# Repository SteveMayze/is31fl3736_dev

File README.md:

# IS31FL3736 Development Board

This project is to develop a prototype for reviewing the IS31FL3736 12×8 DOTS MATRIX LED DRIVER WITH INDIVIDUAL AUTO BREATH FUNCTION from [Integrated Silicon Solution, Inc](www.issi.com)
 The basic goals of this project is to create a simple board with an array of RGB leds to see what is involved to control the LEDs as per the writeup in the datasheet. Things of interest will be
 
 1. Simplicity of use (firmware)
 1. Simplicity of the layout
 1. The effective power consumption
 1. The footprint size.

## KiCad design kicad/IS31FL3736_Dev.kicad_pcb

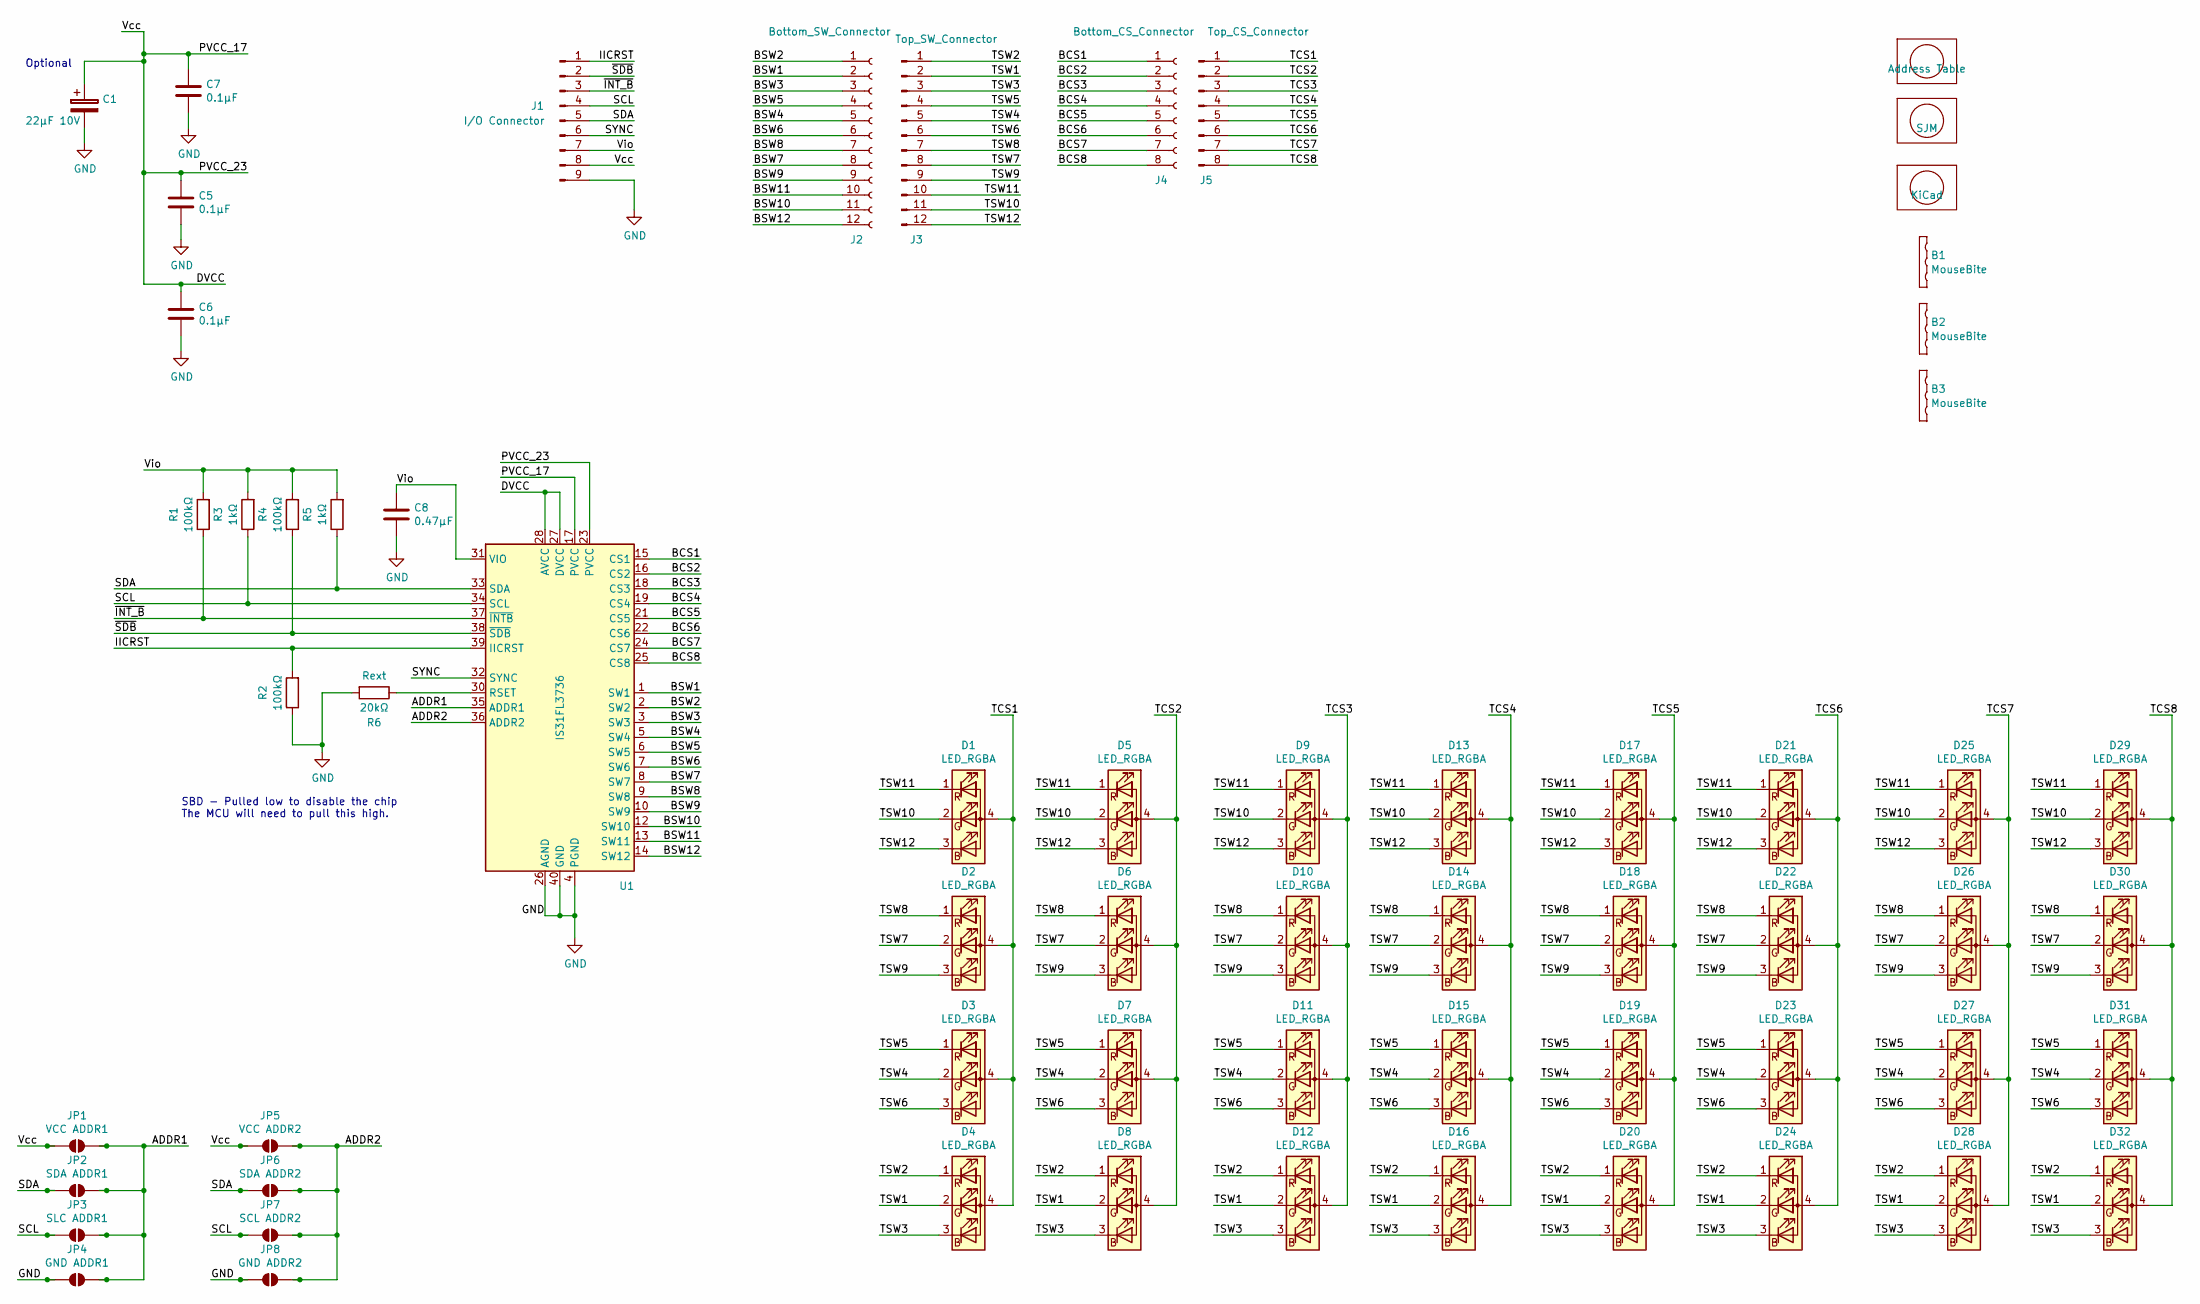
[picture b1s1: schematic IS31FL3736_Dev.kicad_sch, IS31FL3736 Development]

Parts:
B1, B2, B3: MouseBite; MouseBites
C1: 22μF 10V; CP_EIA-2012-15_AVX-P
C5, C6, C7: 0.1μF; C_0805_2012Metric
C8: 0.47μF; C_0805_2012Metric
D1, D2, D3, D4, D5, D6, D7, D8, D9, D10, D11, D12, D13, D14, D15, D16, D17, D18, D19, D20, D21, D22, D23, D24, D25, D26, D27, D28, D29, D30, D31, D32: LED_RGBA; LED_RGB_4-PLCC; MPN AAA3528LSEEZGKQBKS
J1: I/O Connector; PinHeader_1x09_P2.54mm_Horizontal
J2: Bottom_SW_Connector; PinSocket_1x12_P2.54mm_Vertical
J3: Top_SW_Connector; PinHeader_1x12_P2.54mm_Vertical
J4: Bottom_CS_Connector; PinSocket_1x08_P2.54mm_Vertical
J5: Top_CS_Connector; PinHeader_1x08_P2.54mm_Vertical
JP1: VCC ADDR1; SolderJumper-2_P1.3mm_Open_RoundedPad1.0x1.5mm
JP2: SDA ADDR1; SolderJumper-2_P1.3mm_Open_RoundedPad1.0x1.5mm
JP3: SLC ADDR1; SolderJumper-2_P1.3mm_Open_RoundedPad1.0x1.5mm
JP4: GND ADDR1; SolderJumper-2_P1.3mm_Open_RoundedPad1.0x1.5mm
JP5: VCC ADDR2; SolderJumper-2_P1.3mm_Open_RoundedPad1.0x1.5mm
JP6: SDA ADDR2; SolderJumper-2_P1.3mm_Open_RoundedPad1.0x1.5mm
JP7: SCL ADDR2; SolderJumper-2_P1.3mm_Open_RoundedPad1.0x1.5mm
JP8: GND ADDR2; SolderJumper-2_P1.3mm_Open_RoundedPad1.0x1.5mm
Lg1: SJM; MyBasic_rounded_50_1
Lg2: KiCad; KiCad-Logo2_5mm_SilkScreen
Lg3: Address Table; Address_Table
R1, R2, R4: 100kΩ; R_0805_2012Metric
R3, R5: 1kΩ; R_0805_2012Metric
R6: 20kΩ; R_0805_2012Metric
U1: IS31FL3736; QFN-40-1EP_5x5mm_P0.4mm_EP3.6x3.6mm; MPN IS31FL3736

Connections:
/ADDR1: JP1.2 (B), JP2.2 (B), JP3.2 (B), JP4.2 (B), U1.35 (ADDR1)
/ADDR2: JP5.2 (B), JP6.2 (B), JP7.2 (B), JP8.2 (B), U1.36 (ADDR2)
/BCS1: J4.1, U1.15 (CS1)
/BCS2: J4.2, U1.16 (CS2)
/BCS3: J4.3, U1.18 (CS3)
/BCS4: J4.4, U1.19 (CS4)
/BCS5: J4.5, U1.21 (CS5)
/BCS6: J4.6, U1.22 (CS6)
/BCS7: J4.7, U1.24 (CS7)
/BCS8: J4.8, U1.25 (CS8)
/BSW1: J2.2, U1.1 (SW1)
/BSW2: J2.1, U1.2 (SW2)
/BSW3: J2.3, U1.3 (SW3)
/BSW4: J2.5, U1.5 (SW4)
/BSW5: J2.4, U1.6 (SW5)
/BSW6: J2.6, U1.7 (SW6)
/BSW7: J2.8, U1.8 (SW7)
/BSW8: J2.7, U1.9 (SW8)
/BSW9: J2.9, U1.10 (SW9)
/BSW10: J2.11, U1.12 (SW10)
/BSW11: J2.10, U1.13 (SW11)
/BSW12: J2.12, U1.14 (SW12)
/DVCC: C1.1, C5.1, C6.1, C7.1, J1.8, JP1.1 (A), JP5.1 (A), U1.17 (PVCC), U1.23 (PVCC), U1.27 (DVCC), U1.28 (AVCC)
/IICRST: J1.1, R2.2, U1.39 (IICRST)
/SCL: J1.4, JP3.1 (A), JP7.1 (A), R3.1, U1.34 (SCL)
/SDA: J1.5, JP2.1 (A), JP6.1 (A), R5.1, U1.33 (SDA)
/SYNC: J1.6, U1.32 (SYNC)
/TCS1: D1.4 (A), D2.4 (A), D3.4 (A), D4.4 (A), J5.1
/TCS2: D5.4 (A), D6.4 (A), D7.4 (A), D8.4 (A), J5.2
/TCS3: D9.4 (A), D10.4 (A), D11.4 (A), D12.4 (A), J5.3
/TCS4: D13.4 (A), D14.4 (A), D15.4 (A), D16.4 (A), J5.4
/TCS5: D17.4 (A), D18.4 (A), D19.4 (A), D20.4 (A), J5.5
/TCS6: D21.4 (A), D22.4 (A), D23.4 (A), D24.4 (A), J5.6
/TCS7: D25.4 (A), D26.4 (A), D27.4 (A), D28.4 (A), J5.7
/TCS8: D29.4 (A), D30.4 (A), D31.4 (A), D32.4 (A), J5.8
/TSW1: D4.2 (GK), D8.2 (GK), D12.2 (GK), D16.2 (GK), D20.2 (GK), D24.2 (GK), D28.2 (GK), D32.2 (GK), J3.2
/TSW2: D4.1 (RK), D8.1 (RK), D12.1 (RK), D16.1 (RK), D20.1 (RK), D24.1 (RK), D28.1 (RK), D32.1 (RK), J3.1
/TSW3: D4.3 (BK), D8.3 (BK), D12.3 (BK), D16.3 (BK), D20.3 (BK), D24.3 (BK), D28.3 (BK), D32.3 (BK), J3.3
/TSW4: D3.2 (GK), D7.2 (GK), D11.2 (GK), D15.2 (GK), D19.2 (GK), D23.2 (GK), D27.2 (GK), D31.2 (GK), J3.5
/TSW5: D3.1 (RK), D7.1 (RK), D11.1 (RK), D15.1 (RK), D19.1 (RK), D23.1 (RK), D27.1 (RK), D31.1 (RK), J3.4
/TSW6: D3.3 (BK), D7.3 (BK), D11.3 (BK), D15.3 (BK), D19.3 (BK), D23.3 (BK), D27.3 (BK), D31.3 (BK), J3.6
/TSW7: D2.2 (GK), D6.2 (GK), D10.2 (GK), D14.2 (GK), D18.2 (GK), D22.2 (GK), D26.2 (GK), D30.2 (GK), J3.8
/TSW8: D2.1 (RK), D6.1 (RK), D10.1 (RK), D14.1 (RK), D18.1 (RK), D22.1 (RK), D26.1 (RK), D30.1 (RK), J3.7
/TSW9: D2.3 (BK), D6.3 (BK), D10.3 (BK), D14.3 (BK), D18.3 (BK), D22.3 (BK), D26.3 (BK), D30.3 (BK), J3.9
/TSW10: D1.2 (GK), D5.2 (GK), D9.2 (GK), D13.2 (GK), D17.2 (GK), D21.2 (GK), D25.2 (GK), D29.2 (GK), J3.11
/TSW11: D1.1 (RK), D5.1 (RK), D9.1 (RK), D13.1 (RK), D17.1 (RK), D21.1 (RK), D25.1 (RK), D29.1 (RK), J3.10
/TSW12: D1.3 (BK), D5.3 (BK), D9.3 (BK), D13.3 (BK), D17.3 (BK), D21.3 (BK), D25.3 (BK), D29.3 (BK), J3.12
/Vio: C8.1, J1.7, R1.2, R3.2, R4.2, R5.2, U1.31 (VIO)
/~INT_B: J1.3, R1.1, U1.37 (~INTB)
/~SDB: J1.2, R4.1, U1.38 (~SDB)
GND: C1.2, C5.2, C6.2, C7.2, C8.2, J1.9, JP4.1 (A), JP8.1 (A), R2.1, R6.2, U1.4 (PGND), U1.11 (PGND), U1.26 (AGND), U1.40 (GND), U1.41 (GND)
unnamed: R6.1, U1.30 (RSET)

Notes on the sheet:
SBD - Pulled low to disable the chip The MCU will need to pull this high.
Optional

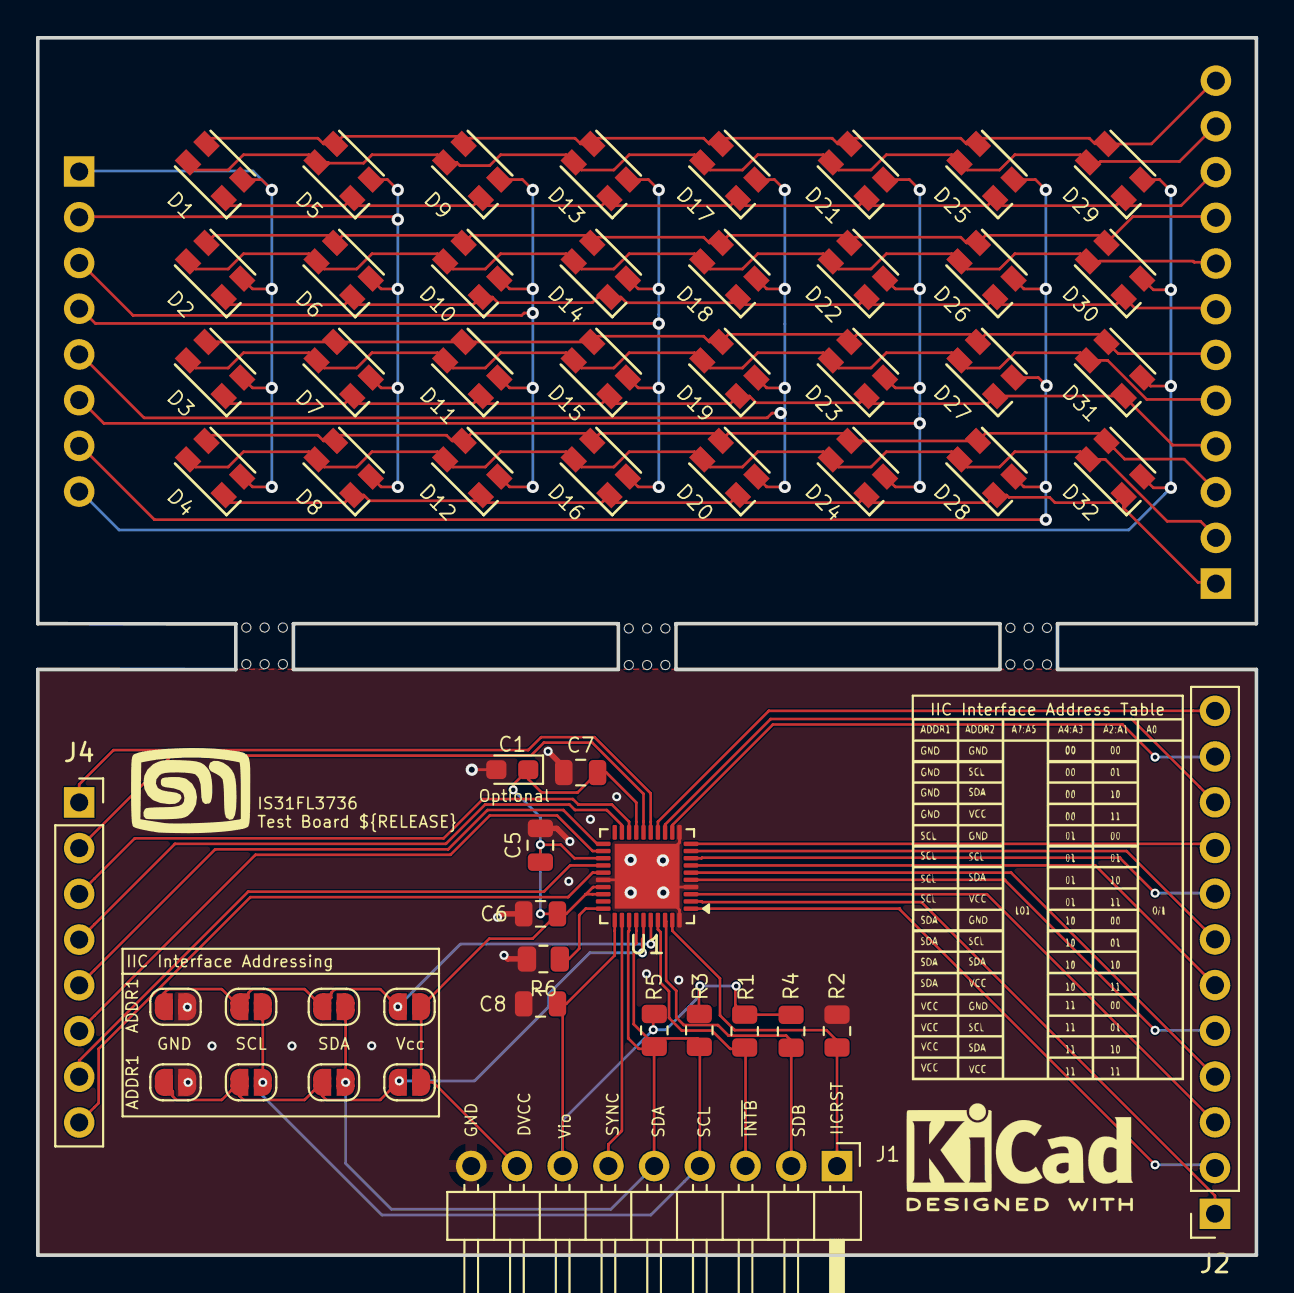
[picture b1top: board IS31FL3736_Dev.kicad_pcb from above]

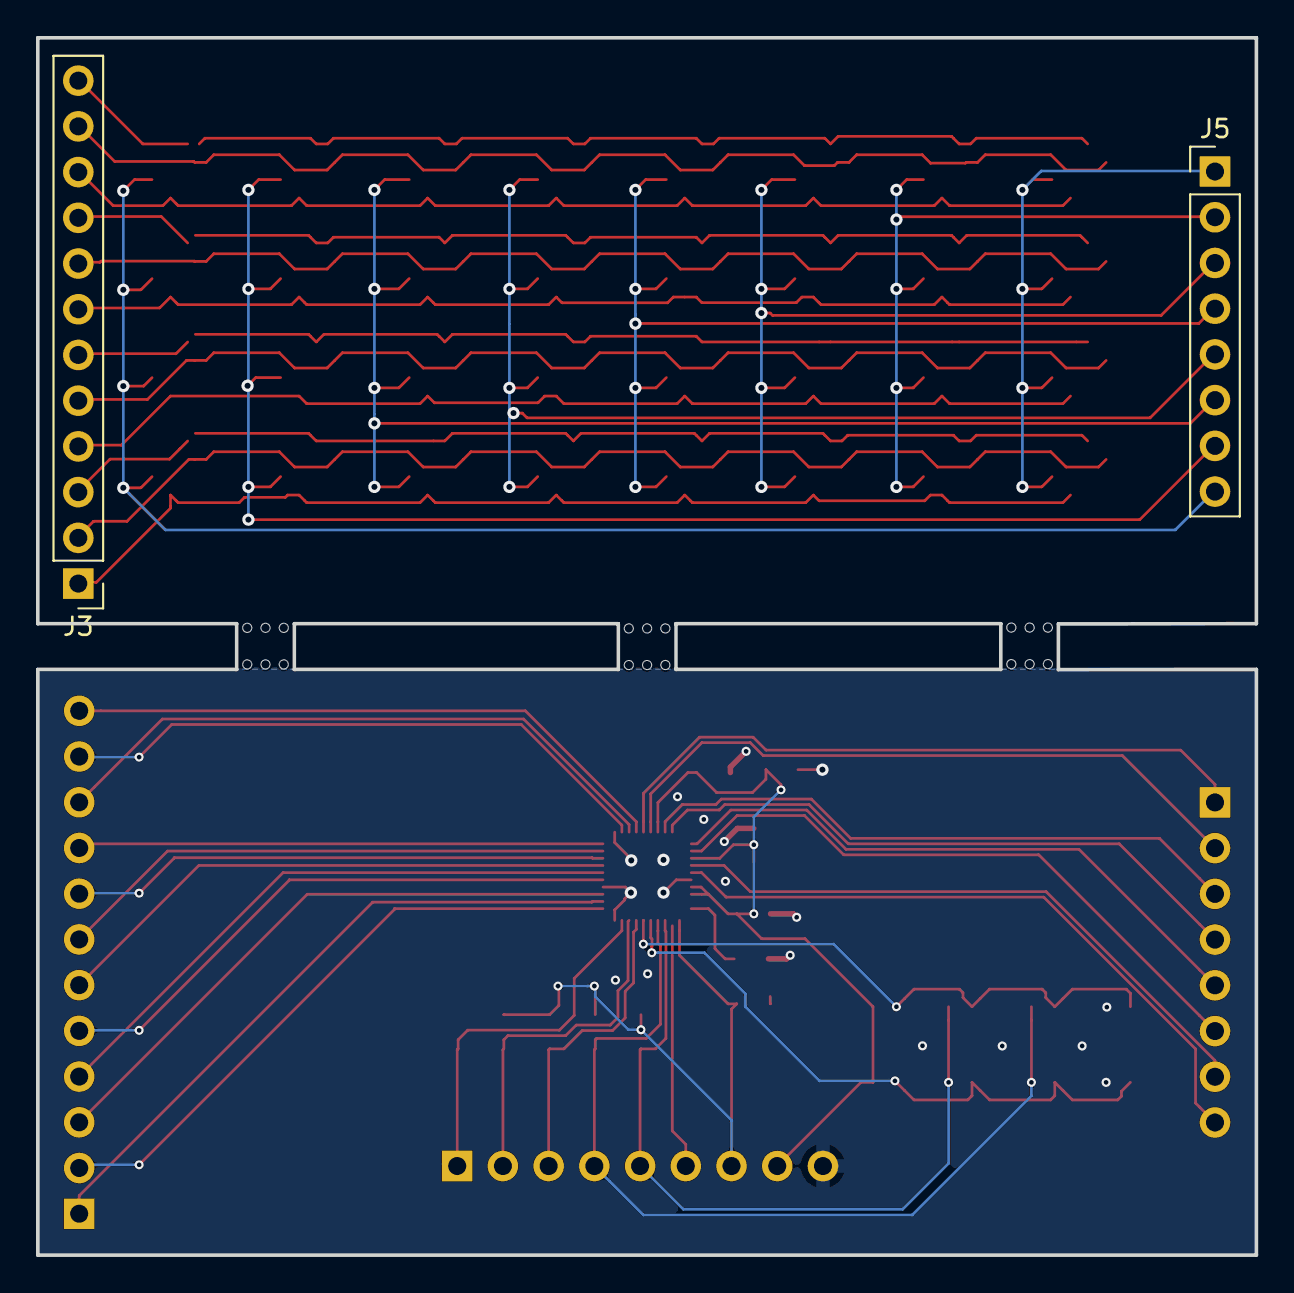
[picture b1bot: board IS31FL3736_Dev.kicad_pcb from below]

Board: 2 copper layers, 67.7 x 67.6 mm, 63 parts (2 on the bottom side), 52 nets.

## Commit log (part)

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2019-12-30 Created the README.md
2019-12-31 Schematic and initial layout
2020-01-27 Board update
2020-04-05 Layout done
2020-10-04 Adding the firmware
2020-10-04 Update to SBD pullup
